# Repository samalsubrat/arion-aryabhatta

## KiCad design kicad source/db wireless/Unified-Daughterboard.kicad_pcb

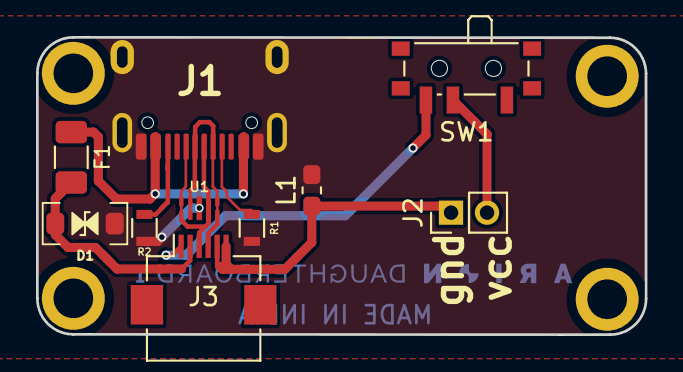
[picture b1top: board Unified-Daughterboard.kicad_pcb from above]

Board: 2 copper layers, 33.8 x 16.5 mm, 14 parts (0 on the bottom side), 10 nets.

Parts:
D1: SMF9.0CA; D_SOD-123_Bidirectional
F1: ASMD1206-150; Fuse_1206_3216Metric
J1: TYPE-C-31-M12_13; TYPE-C-31-M-12
J2: Conn_01x02_Socket; PinHeader_1x02_P2.00mm_Vertical
J3: Conn_01x06_Pin; Hirose_FH12-6S-0.5SH_1x06-1MP_P0.50mm_Horizontal
L1: 60R@100MHz; L_0603_1608Metric_Pad1.05x0.95mm_HandSolder
MH1, MH3, MH4, MH4#2: Mount-M2; Generic-Mounthole
R1, R2: 5.1k; R_0603
SW1: SW_DPDT_x2; SW_SPDT_PCM12
U1: TPD4E05U06DQAR; USON-10_2.5x1.0mm_P0.5mm

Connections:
DA+: J1.A6 (D+), J1.B6 (D+), J3.3, U1.1 (IO1), U1.4 (D2+), U1.7 (NC), U1.10 (NC)
DA-: J1.A7 (D-), J1.B7 (D-), J3.4, U1.2 (IO2), U1.5 (D2-), U1.6 (NC), U1.9 (NC)
GND: J2.1, J3.5, J3.6, L1.1
GNDPWR: D1.1 (A1), J1.A1 (GND), J1.B1 (GND), J1.S (SHIELD), L1.2, R1.2, R2.2, U1.3 (GND), U1.8 (GND)
unnamed: J1.A5 (CC1), R1.1
unnamed: J1.B5 (CC2), R2.1
VBUS: F1.1, J1.A4 (VBUS), J1.B4 (VBUS)
VCC: D1.2 (A2), F1.2, J3.2
bat in: J2.2, SW1.2 (B)
bat+: J3.1, SW1.3 (C)

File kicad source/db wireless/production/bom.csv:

+//3//f/9-Designator,Footprint,Quantity,Value,LCSC Part +ACM-
D1,D+AF8-SOD+AC0-123+AF8-Bidirectional,1,SMF9.0CA,
F1,1206,1,ASMD1206+AC0-150,
J1,TYPE+AC0-C+AC0-31+AC0-M+AC0-12,1,TYPE+AC0-C+AC0-31+AC0-M12+AF8-13,
J2,PinHeader+AF8-1x02+AF8-P2.54mm+AF8-Vertical,1,Conn+AF8-01x02+AF8-Socket,
J3,Hirose+AF8-FH12+AC0-6S+AC0-0.5SH+AF8-1x06+AC0-1MP+AF8-P0.50mm+AF8-Horizontal,1,Conn+AF8-01x06+AF8-Pin,
L1,603,1,60R+AEA-100MHz,
+ACI-MH1, MH3, MH4+AF8-2, MH4+ACI-,Generic+AC0-Mounthole,4,Mount+AC0-M2,
+ACI-R1, R2+ACI-,R+AF8-0603,2,5.1k,
SW1,SW+AF8-SPDT+AF8-PCM12,1,MSK12C02,
U1,USON+AC0-10+AF8-2.5x1.0mm+AF8-P0.5mm,1,TPD4E05U06DQAR,

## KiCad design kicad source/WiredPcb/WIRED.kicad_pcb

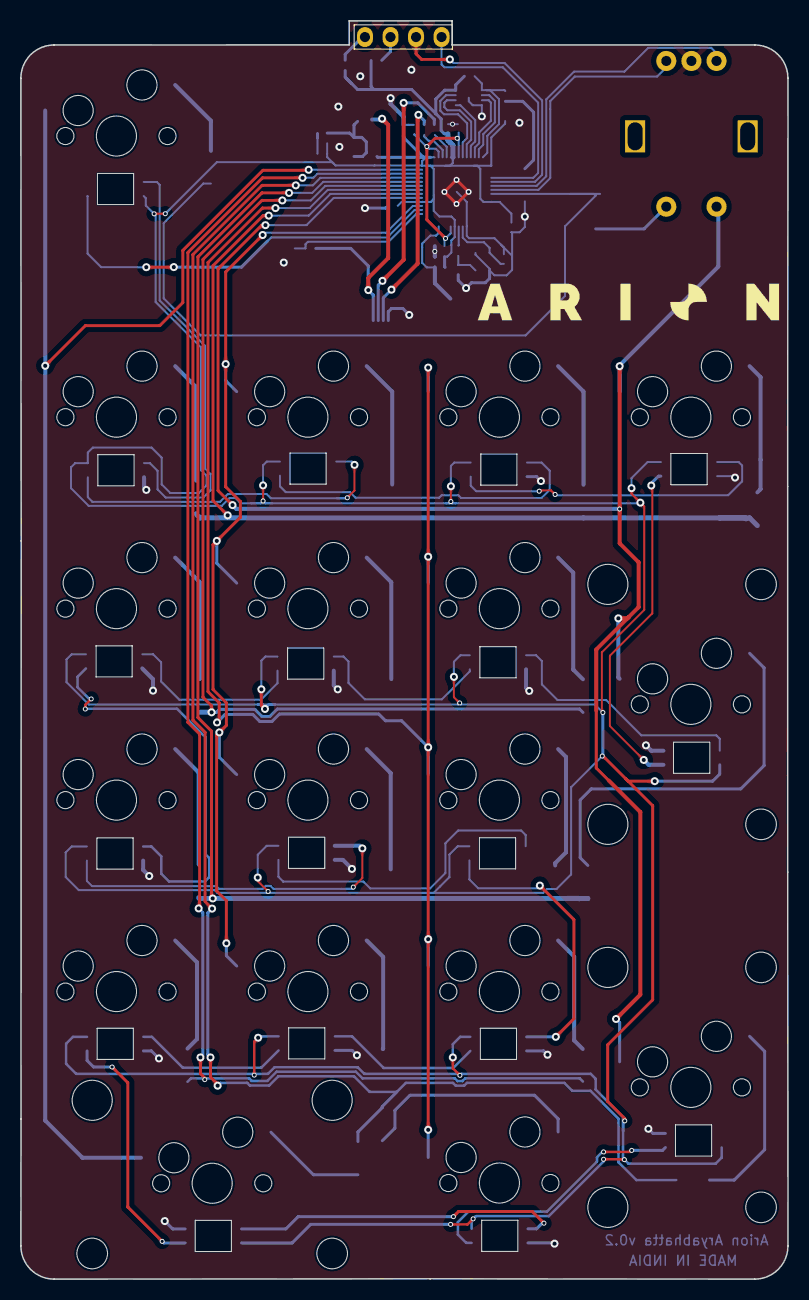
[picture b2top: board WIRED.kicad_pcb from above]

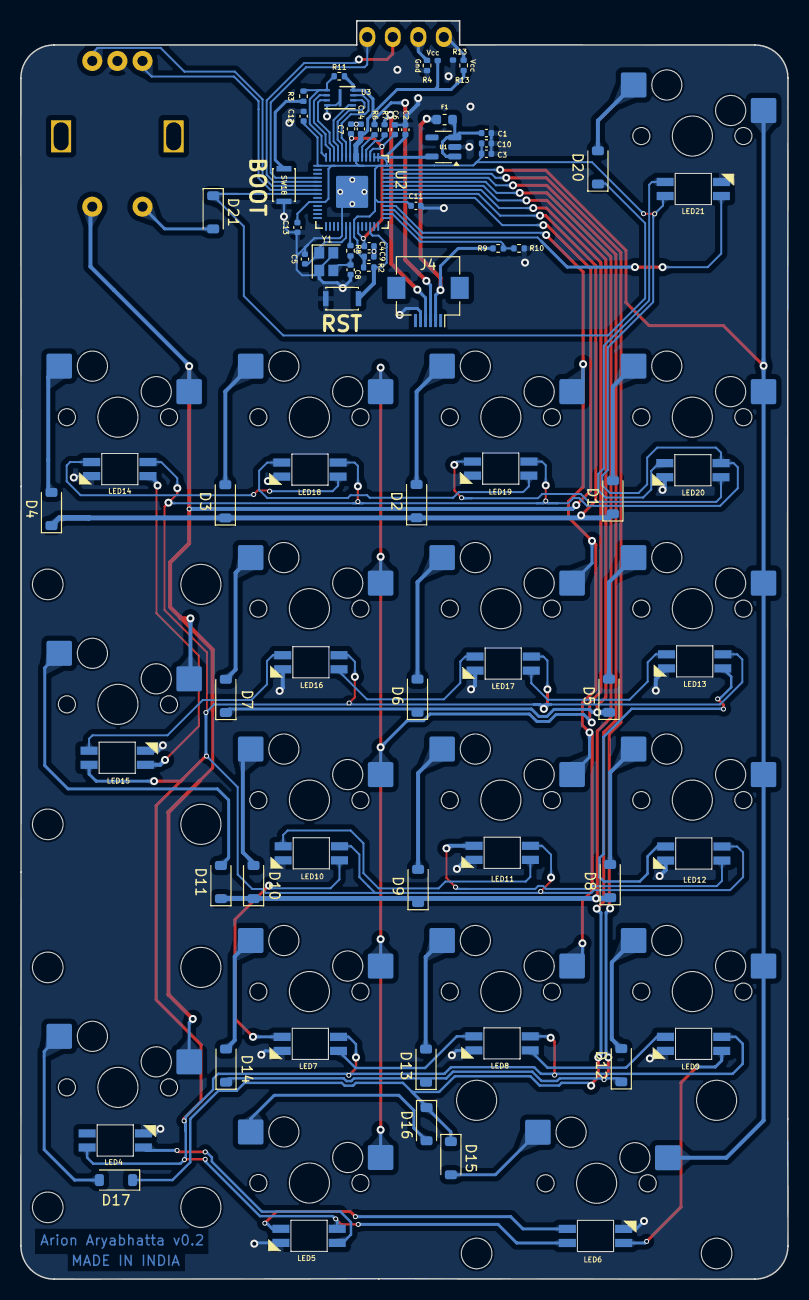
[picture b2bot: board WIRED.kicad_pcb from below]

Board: 2 copper layers, 76.3 x 125.2 mm, 91 parts (89 on the bottom side), 74 nets.

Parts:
C1, C2, C3, C4: 1µ; C_0402_1005Metric
C5, C8: 15p; C_0402_1005Metric
C6, C7, C9, C10, C11, C12, C13, C14: 100n; C_0402_1005Metric
D1, D2, D3, D4, D5, D6, D7, D8, D9, D10, D11, D12, D13, D14, D15, D16, D17, D20, D21: 1N4148W; D_SOD-123
F1: Polyfuse; Fuse_0603_1608Metric
J3: Conn_01x04_Pin; 128x64OLED
J4: Conn_01x06_Socket; Hirose_FH12-6S-0.5SH_1x06-1MP_P0.50mm_Horizontal
LED4, LED5, LED6, LED7, LED8, LED9, LED10, LED11, LED12, LED13, LED14, LED15, LED16, LED17, LED18, LED19, LED20, LED21: YS-SK6812MINI-E
R1, R4, R12, R13: 0k; R_0402_1005Metric
R2, R10, R11: 10k; R_0402_1005Metric
R3, R8: 1k; R_0402_1005Metric
R6, R7: 27; R_0402_1005Metric
R9: 5.1k; R_0402_1005Metric
SW0, SW1, SW2, SW3, SW4, SW5, SW6, SW8, SW9, SW10, SW11, SW12, SW13, SW16, SW20: KEYSW; MX-Hotswap-1U
SW7, SW14: KEYSW; MX-Hotswap-2U-Vertical-ReversedStabilizers
SW15: KEYSW; MX-Hotswap-2U-ReversedStabilizers
SW17, SW18: SW_Push; SW_SPST_CK_KXT3
SW19: Rotary_Encoder_Switch; RotaryEncoder_Alps_EC11E-Switch_Vertical_H20mm-keebio_modif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
U1: XC6210B332MR-G; SOT-23-5
U2: U2; QFN-56-1EP_7x7mm_P0.4mm_EP3.2x3.2mm
U3: U3; USON-8-1EP_3x2mm_P0.5mm_EP0.25x1.65mm
Y1: Crystal_GND24; Crystal_SMD_2520-4Pin_2.5x2.0mm

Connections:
+1V1: C4.1, C6.1, C7.1, U2.23 (DVDD), U2.45 (VREG_VOUT), U2.50 (DVDD)
+3V3: C2.1, C3.1, C9.1, C10.1, C11.1, C12.1, C13.1, C14.1, LED4.1 (VDD), LED5.1 (VDD), LED6.1 (VDD), LED7.1 (VDD), LED8.1 (VDD), LED9.1 (VDD), LED10.1 (VDD), LED11.1 (VDD), LED12.1 (VDD), LED13.1 (VDD), LED14.1 (VDD), LED15.1 (VDD), LED16.1 (VDD), LED17.1 (VDD), LED18.1 (VDD), LED19.1 (VDD), LED20.1 (VDD), LED21.1 (VDD), R1.2, R2.2, R11.2, R13.2, U1.5 (VOUT), U2.1 (IOVDD), U2.10 (IOVDD), U2.22 (IOVDD), U2.33 (IOVDD), U2.42 (IOVDD), U2.43 (ADC_AVDD), U2.44 (VREG_IN), U2.48 (USB_VDD), U2.49 (IOVDD), U3.8 (VCC)
+5V: C1.1, F1.2, U1.1 (VIN), U1.3 (EN)
/D+: J4.3, R6.1
/D-: J4.4, R7.1
/QSPI_D0: U2.53 (QSPI_SD0), U3.5 (DI(IO0))
/QSPI_D1: U2.55 (QSPI_SD1), U3.2 (DO(IO1))
/QSPI_D2: U2.54 (QSPI_SD2), U3.3 (IO2)
/QSPI_D3: U2.51 (QSPI_SD3), U3.7 (IO3)
/QSPI_SCLK: U2.52 (QSPI_SCLK), U3.6 (CLK)
/QSPI_~CS: R3.2, R11.1, U2.56 (QSPI_SS), U3.1 (~CS)
/VBUS_DET: R9.1, R10.2, U2.30 (GPIO19)
/~RESET: R2.1, SW17.2, U2.26 (RUN/~RST)
ENCA: SW19.A, U2.6 (GPIO4)
ENCB: SW19.B, U2.7 (GPIO5)
GND: C1.2, C2.2, C3.2, C4.2, C5.2, C6.2, C7.2, C8.2, C9.2, C10.2, C11.2, C12.2, C13.2, C14.2, J4.5, LED4.3 (VSS), LED5.3 (VSS), LED6.3 (VSS), LED7.3 (VSS), LED8.3 (VSS), LED9.3 (VSS), LED10.3 (VSS), LED11.3 (VSS), LED12.3 (VSS), LED13.3 (VSS), LED14.3 (VSS), LED15.3 (VSS), LED16.3 (VSS), LED17.3 (VSS), LED18.3 (VSS), LED19.3 (VSS), LED20.3 (VSS), LED21.3 (VSS), R4.1, R10.1, R12.1, SW17.1, SW18.1, SW19.C, U1.2 (GND), U2.19 (TESTEN), U2.57 (GND), U3.4 (GND), U3.9 (EP), Y1.2, Y1.4
LEDIN: LED21.4 (DIN), U2.31 (GPIO20)
unnamed: C8.1, R8.1, Y1.3
unnamed: D1.2 (A), SW0.2
unnamed: D2.2 (A), SW1.2
unnamed: D3.2 (A), SW2.2
unnamed: D4.2 (A), SW3.2
unnamed: D5.2 (A), SW4.2
unnamed: D6.2 (A), SW5.2
unnamed: D7.2 (A), SW6.2
unnamed: D8.2 (A), SW8.2
unnamed: D9.2 (A), SW9.2
unnamed: D10.2 (A), SW10.2
unnamed: D11.2 (A), SW7.2
unnamed: D12.2 (A), SW11.2
unnamed: D13.2 (A), SW12.2
unnamed: D14.2 (A), SW13.2
unnamed: D15.2 (A), SW15.2
unnamed: D16.2 (A), SW16.2
unnamed: D17.2 (A), SW14.2
unnamed: D20.2 (A), SW20.2
unnamed: D21.2 (A), SW19.S1
unnamed: J3.1, R13.1
unnamed: J3.2, R4.2
unnamed: LED4.4 (DIN), LED5.2 (DOUT)
unnamed: LED5.4 (DIN), LED6.2 (DOUT)
unnamed: LED6.4 (DIN), LED9.2 (DOUT)
unnamed: LED7.2 (DOUT), LED8.4 (DIN)
unnamed: LED8.2 (DOUT), LED9.4 (DIN)
unnamed: LED10.4 (DIN), LED11.2 (DOUT)
unnamed: LED7.4 (DIN), LED10.2 (DOUT)
unnamed: LED11.4 (DIN), LED12.2 (DOUT)
unnamed: LED12.4 (DIN), LED13.2 (DOUT)
unnamed: LED13.4 (DIN), LED17.2 (DOUT)
unnamed: LED14.4 (DIN), LED18.2 (DOUT)
unnamed: LED14.2 (DOUT), LED15.4 (DIN)
unnamed: LED15.2 (DOUT), LED16.4 (DIN)
unnamed: LED16.2 (DOUT), LED17.4 (DIN)
unnamed: LED18.4 (DIN), LED19.2 (DOUT)
unnamed: LED19.4 (DIN), LED20.2 (DOUT)
unnamed: LED20.4 (DIN), LED21.2 (DOUT)
unnamed: R3.1, SW18.2
unnamed: R7.2, U2.46 (USB_DM)
unnamed: R6.2, U2.47 (USB_DP)
unnamed: C5.1, U2.20 (XIN), Y1.1
unnamed: R8.2, U2.21 (XOUT)
VBUS: F1.1, J4.2, R9.2
col0: SW0.1, SW4.1, SW8.1, SW11.1, SW15.1, SW20.1, U2.41 (GPIO29_ADC3)
col1: SW1.1, SW5.1, SW9.1, SW12.1, U2.32 (GPIO21)
col2: SW2.1, SW6.1, SW10.1, SW13.1, SW16.1, U2.36 (GPIO24)
col3: SW3.1, SW7.1, SW14.1, SW19.S2, U2.34 (GPIO22)
row0: D1.1 (K), D2.1 (K), D3.1 (K), D4.1 (K), U2.35 (GPIO23)
row1: D5.1 (K), D6.1 (K), D7.1 (K), U2.37 (GPIO25)
row2: D8.1 (K), D9.1 (K), D10.1 (K), D11.1 (K), U2.38 (GPIO26_ADC0)
row3: D12.1 (K), D13.1 (K), D14.1 (K), U2.40 (GPIO28_ADC2)
row4: D15.1 (K), D16.1 (K), D17.1 (K), U2.39 (GPIO27_ADC1)
row5: D20.1 (K), D21.1 (K), U2.8 (GPIO6)
sda: J3.4, U2.4 (GPIO2)
sdl: J3.3, U2.5 (GPIO3)

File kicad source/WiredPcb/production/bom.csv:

+//3//f/9-Designator,Footprint,Quantity,Value,LCSC Part +ACM-
+ACI-C1, C2+ACI-,402,2,1U,C19666
+ACI-C10, C11, C12, C13, C14, C6, C7, C9+ACI-,402,8,100n,C1525
+ACI-C3, C4+ACI-,402,2,1U,C52923
+ACI-C5, C8+ACI-,402,2,15p,C1548
+ACI-D1, D10, D11, D12, D13, D14, D15, D16, D17, D2, D20, D21, D3, D4, D5, D6, D7, D8, D9+ACI-,D+AF8-SOD+AC0-123,19,1N4148W,
F1,603,1,Polyfuse,C69679
,,,,
J4,Hirose+AF8-FH12+AC0-6S+AC0-0.5SH+AF8-1x06+AC0-1MP+AF8-P0.50mm+AF8-Horizontal,1,Conn+AF8-01x06+AF8-Socket,
+ACI-LED10, LED11, LED12, LED13, LED14, LED15, LED16, LED17, LED18, LED19, LED20, LED21, LED4, LED5, LED6, LED7, LED8, LED9+ACI-,YS+AC0-SK6812MINI+AC0-E,18,SK6812MINI+AC0-E,
,,,,
+ACI-R10, R11, R2+ACI-,402,3,10k,C25744
+ACI-R3, R8+ACI-,402,2,1k,C11702
+ACI-R6, R7+ACI-,402,2,27,C25100
R9,402,1,5.1k,C25905
+ACI-SW0, SW1, SW10, SW11, SW12, SW13, SW16, SW2, SW20, SW3, SW4, SW5, SW6, SW8, SW9+ACI-,MXOnly+AC0-1U+AC0-Hotswap+AC0-Antishear,15,KEYSW,
+ACI-SW14, SW15, SW7+ACI-,MXOnly+AC0-2U+AC0-Hotswap,3,KEYSW,
+ACI-SW17, SW18+ACI-,SW+AF8-SPST+AF8-CK+AF8-KXT3,2,SW+AF8-Push,C319433
SW19,RotaryEncoder+AF8-Alps+AF8-EC11E+AC0-Switch+AF8-Vertical+AF8-H20mm+AC0-keebio+AF8-modified,1,Rotary+AF8-Encoder+AF8-Switch,
U1,SOT+AC0-23+AC0-5,1,XC6210B332MR+AC0-G,C82942
U2,QFN+AC0-56+AC0-1EP+AF8-7x7mm+AF8-P0.4mm+AF8-EP3.2x3.2mm,1,RP2040,C2040
U3,USON+AC0-8+AC0-1EP+AF8-3x2mm+AF8-P0.5mm+AF8-EP0.25x1.65mm,1,W25Q16JVUXIQ,C2843335
Y1,Crystal+AF8-SMD+AF8-2520+AC0-4Pin+AF8-2.5x2.0mm,1,Crystal+AF8-GND24,C2149204

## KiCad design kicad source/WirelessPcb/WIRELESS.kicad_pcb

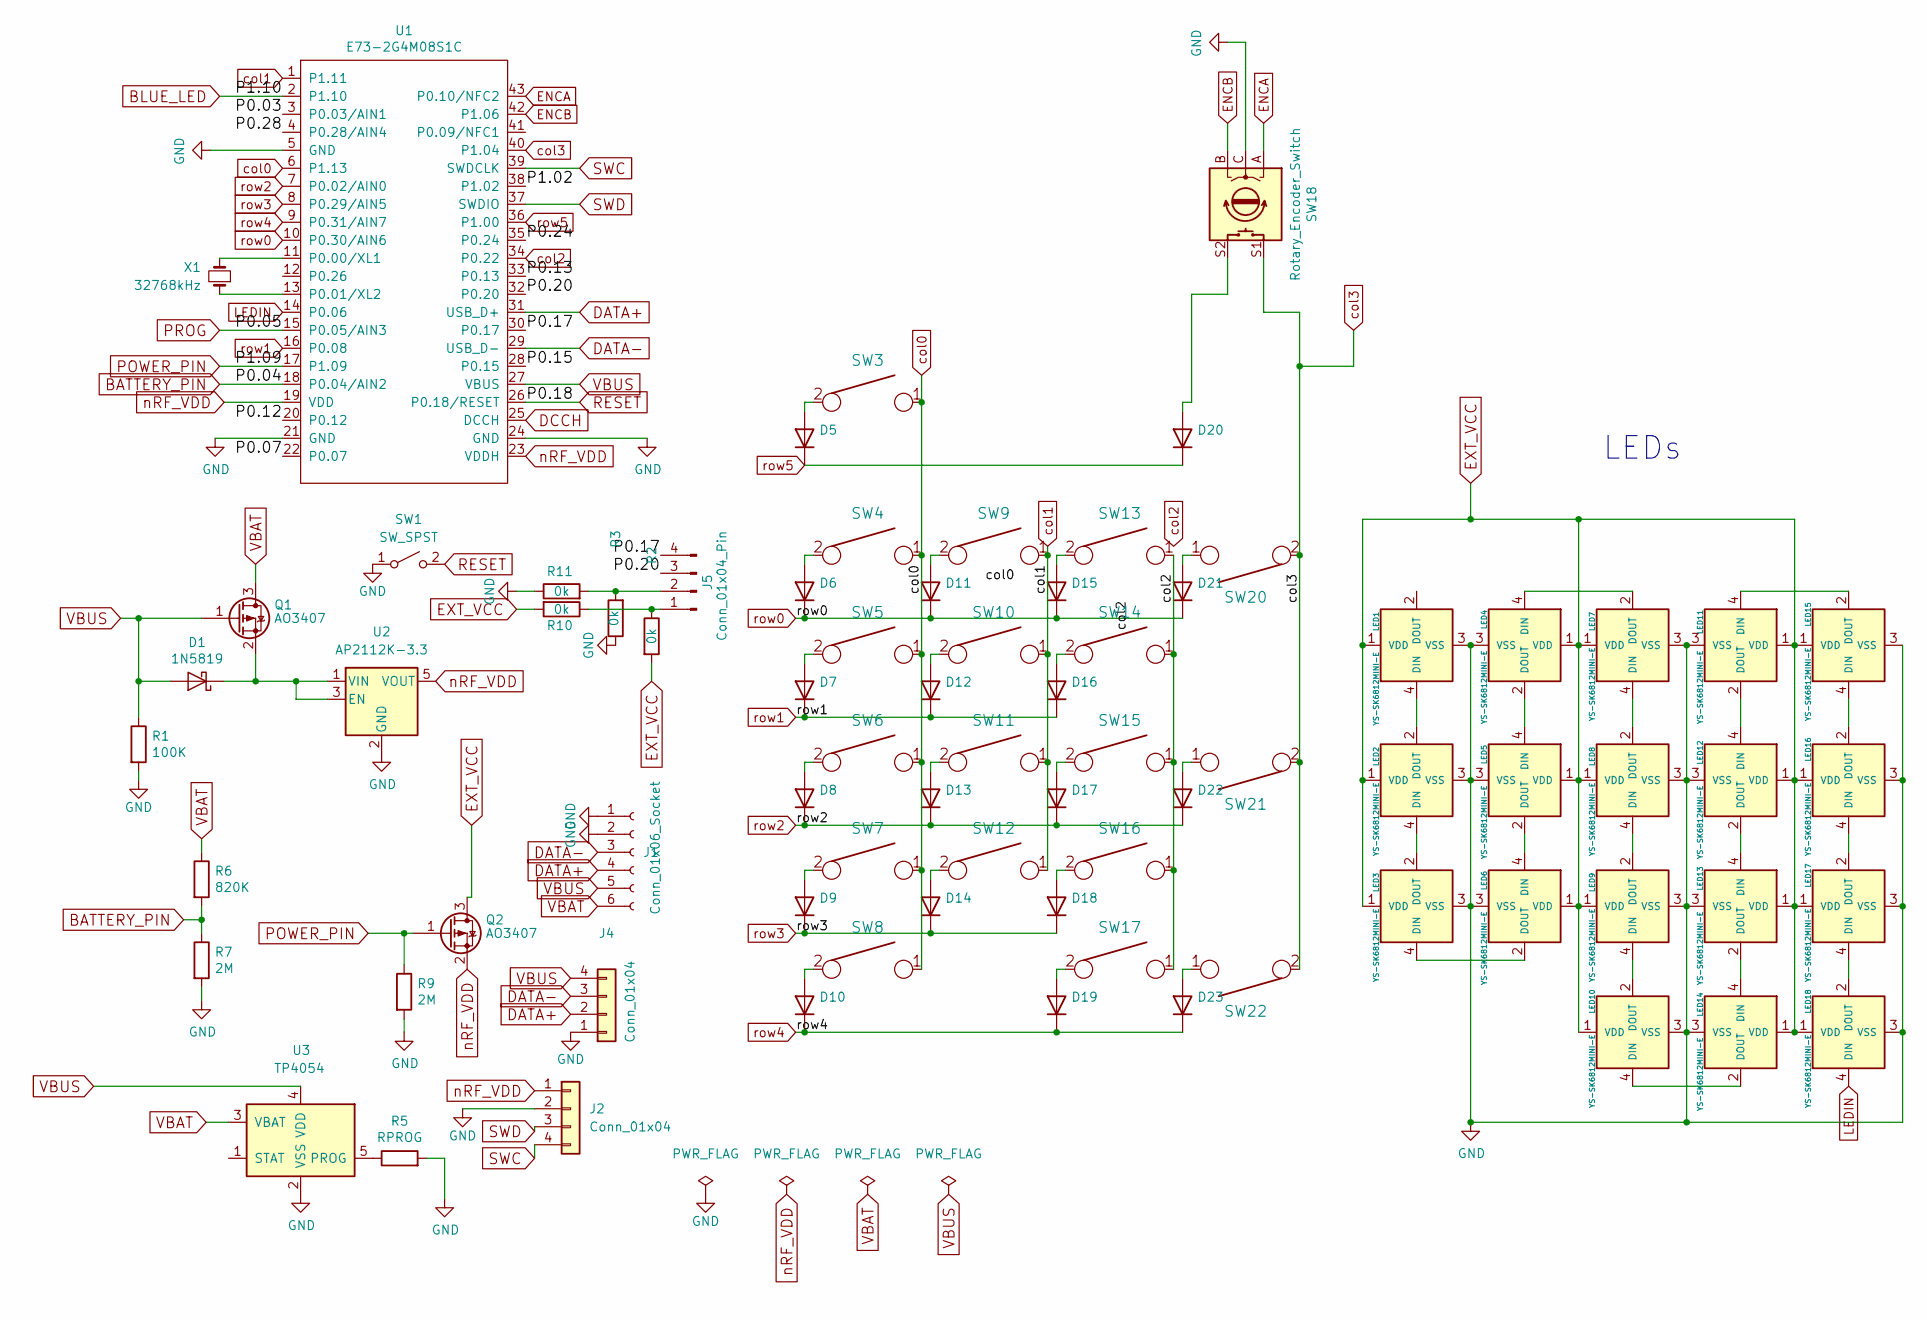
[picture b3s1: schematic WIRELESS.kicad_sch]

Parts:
D1: 1N5819; D_SOD-323F
D5, D6, D7, D8, D9, D10, D11, D12, D13, D14, D15, D16, D17, D18, D19, D20, D21, D22, D23: D_SOD-123
J1: Conn_01x06_Socket; Hirose_FH12-6S-0.5SH_1x06-1MP_P0.50mm_Horizontal
J2, J4: Conn_01x04; PinHeader_1x04_P2.54mm_Vertical
J5: Conn_01x04_Pin; PinHeader_1x04_P2.54mm_Vertical
LED1, LED2, LED3, LED4, LED5, LED6, LED7, LED8, LED9, LED10, LED11, LED12, LED13, LED14, LED15, LED16, LED17, LED18: YS-SK6812MINI-E
Q1, Q2: AO3407; SOT-23
R1: 100K; R_0603_1608Metric
R2, R3, R10, R11: 0k; R_0402_1005Metric; LCSC C25744
R5: RPROG; R_0603_1608Metric
R6: 820K; R_0603_1608Metric
R7, R9: 2M; R_0603_1608Metric
SW1: SW_SPST; SW_SPST_CK_KXT3
SW3, SW4, SW5, SW6, SW7, SW9, SW10, SW11, SW12, SW13, SW14, SW15, SW16, SW17, SW20: KEYSW; MX-Hotswap-1U
SW8: KEYSW; MX-Hotswap-2U-ReversedStabilizers
SW18: Rotary_Encoder_Switch; RotaryEncoder_Alps_EC11E-Switch_Vertical_H20mm-keebio_modif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
SW21, SW22: KEYSW; MX-Hotswap-2U-Vertical-ReversedStabilizers
U1: E73-2G4M08S1C; E73-2G4M08S1C-52840
U2: AP2112K-3.3; SOT-23-5
U3: TP4054; SOT-23-5
X1: 32768kHz

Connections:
/P0.03: U1.3 (P0.03/AIN1)
/P0.07: U1.22 (P0.07)
/P0.12: U1.20 (P0.12)
/P0.13: U1.33 (P0.13)
/P0.15: U1.28 (P0.15)
/P0.17: J5.4, U1.30 (P0.17)
/P0.20: J5.3, U1.32 (P0.20)
/P0.24: U1.35 (P0.24)
/P0.28: U1.4 (P0.28/AIN4)
/P1.02: U1.38 (P1.02)
BATTERY_PIN: R6.2, R7.1, U1.18 (P0.04/AIN2)
BLUE_LED: U1.2 (P1.10)
DATA+: J1.4, J4.2, U1.31 (USB_D+)
DATA-: J1.3, J4.3, U1.29 (USB_D-)
DCCH: U1.25 (DCCH)
ENCA: SW18.A, U1.43 (P0.10/NFC2)
ENCB: SW18.B, U1.42 (P1.06)
EXT_VCC: LED1.1 (VDD), LED2.1 (VDD), LED3.1 (VDD), LED4.1 (VDD), LED5.1 (VDD), LED6.1 (VDD), LED7.1 (VDD), LED8.1 (VDD), LED9.1 (VDD), LED10.1 (VDD), LED11.1 (VDD), LED12.1 (VDD), LED13.1 (VDD), LED14.1 (VDD), LED15.1 (VDD), LED16.1 (VDD), LED17.1 (VDD), LED18.1 (VDD), Q2.3 (D), R2.2, R10.2
GND: J1.1, J1.2, J2.2, J4.1, LED1.3 (VSS), LED2.3 (VSS), LED3.3 (VSS), LED4.3 (VSS), LED5.3 (VSS), LED6.3 (VSS), LED7.3 (VSS), LED8.3 (VSS), LED9.3 (VSS), LED10.3 (VSS), LED11.3 (VSS), LED12.3 (VSS), LED13.3 (VSS), LED14.3 (VSS), LED15.3 (VSS), LED16.3 (VSS), LED17.3 (VSS), LED18.3 (VSS), R1.2, R3.1, R5.2, R7.2, R9.2, R11.1, SW1.1 (A), SW18.C, U1.5 (GND), U1.21 (GND), U1.24 (GND), U2.2 (GND), U3.2 (VSS); also elsewhere on the board
LEDIN: LED18.4 (DIN), U1.14 (P0.06)
unnamed: D1.1 (K), Q1.2 (S), U2.1 (VIN), U2.3 (EN)
unnamed: D5.2 (A), SW3.2
unnamed: D6.2 (A), SW4.2
unnamed: D7.2 (A), SW5.2
unnamed: D8.2 (A), SW6.2
unnamed: D9.2 (A), SW7.2
unnamed: D10.2 (A), SW8.2
unnamed: D11.2 (A), SW9.2
unnamed: D12.2 (A), SW10.2
unnamed: D13.2 (A), SW11.2
unnamed: D14.2 (A), SW12.2
unnamed: D15.2 (A), SW13.2
unnamed: D16.2 (A), SW14.2
unnamed: D17.2 (A), SW15.2
unnamed: D18.2 (A), SW16.2
unnamed: D19.2 (A), SW17.2
unnamed: D20.2 (A), SW18.S2
unnamed: D21.2 (A), SW20.1
unnamed: D22.2 (A), SW21.1
unnamed: D23.2 (A), SW22.1
unnamed: J5.1, R2.1, R10.1
unnamed: J5.2, R3.2, R11.2
unnamed: LED1.4 (DIN), LED2.2 (DOUT)
unnamed: LED2.4 (DIN), LED3.2 (DOUT)
unnamed: LED3.4 (DIN), LED6.2 (DOUT)
unnamed: LED4.4 (DIN), LED7.2 (DOUT)
unnamed: LED4.2 (DOUT), LED5.4 (DIN)
unnamed: LED5.2 (DOUT), LED6.4 (DIN)
unnamed: LED7.4 (DIN), LED8.2 (DOUT)
unnamed: LED8.4 (DIN), LED9.2 (DOUT)
unnamed: LED10.4 (DIN), LED14.2 (DOUT)
unnamed: LED9.4 (DIN), LED10.2 (DOUT)
unnamed: LED11.4 (DIN), LED15.2 (DOUT)
unnamed: LED11.2 (DOUT), LED12.4 (DIN)
unnamed: LED12.2 (DOUT), LED13.4 (DIN)
unnamed: LED13.2 (DOUT), LED14.4 (DIN)
unnamed: LED15.4 (DIN), LED16.2 (DOUT)
unnamed: LED16.4 (DIN), LED17.2 (DOUT)
unnamed: LED17.4 (DIN), LED18.2 (DOUT)
unnamed: U1.11 (P0.00/XL1), X1.2
unnamed: U1.13 (P0.01/XL2), X1.1
unnamed: R5.1, U3.5 (PROG)
POWER_PIN: Q2.1 (G), R9.1, U1.17 (P1.09)
PROG: U1.15 (P0.05/AIN3)
RESET: SW1.2 (B), U1.26 (P0.18/RESET); also elsewhere on the board
SWC: J2.4, U1.39 (SWDCLK)
SWD: J2.3, U1.37 (SWDIO)
VBAT: J1.6, Q1.3 (D), R6.1, U3.3 (VBAT)
VBUS: D1.2 (A), J1.5, J4.4, Q1.1 (G), R1.1, U1.27 (VBUS), U3.4 (VDD)
col0: SW3.1, SW4.1, SW5.1, SW6.1, SW7.1, SW8.1, U1.6 (P1.13)
col1: SW9.1, SW10.1, SW11.1, SW12.1, U1.1 (P1.11)
col2: SW13.1, SW14.1, SW15.1, SW16.1, SW17.1, U1.34 (P0.22)
col3: SW18.S1, SW20.2, SW21.2, SW22.2, U1.40 (P1.04)
nRF_VDD: J2.1, Q2.2 (S), U1.19 (VDD), U1.23 (VDDH), U2.5 (VOUT)
row0: D6.1 (K), D11.1 (K), D15.1 (K), D21.1 (K), U1.10 (P0.30/AIN6)
row1: D7.1 (K), D12.1 (K), D16.1 (K), U1.16 (P0.08)
row2: D8.1 (K), D13.1 (K), D17.1 (K), D22.1 (K), U1.7 (P0.02/AIN0)
row3: D9.1 (K), D14.1 (K), D18.1 (K), U1.8 (P0.29/AIN5)
row4: D10.1 (K), D19.1 (K), D23.1 (K), U1.9 (P0.31/AIN7)
row5: D5.1 (K), D20.1 (K), U1.36 (P1.00)

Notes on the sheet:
LEDs

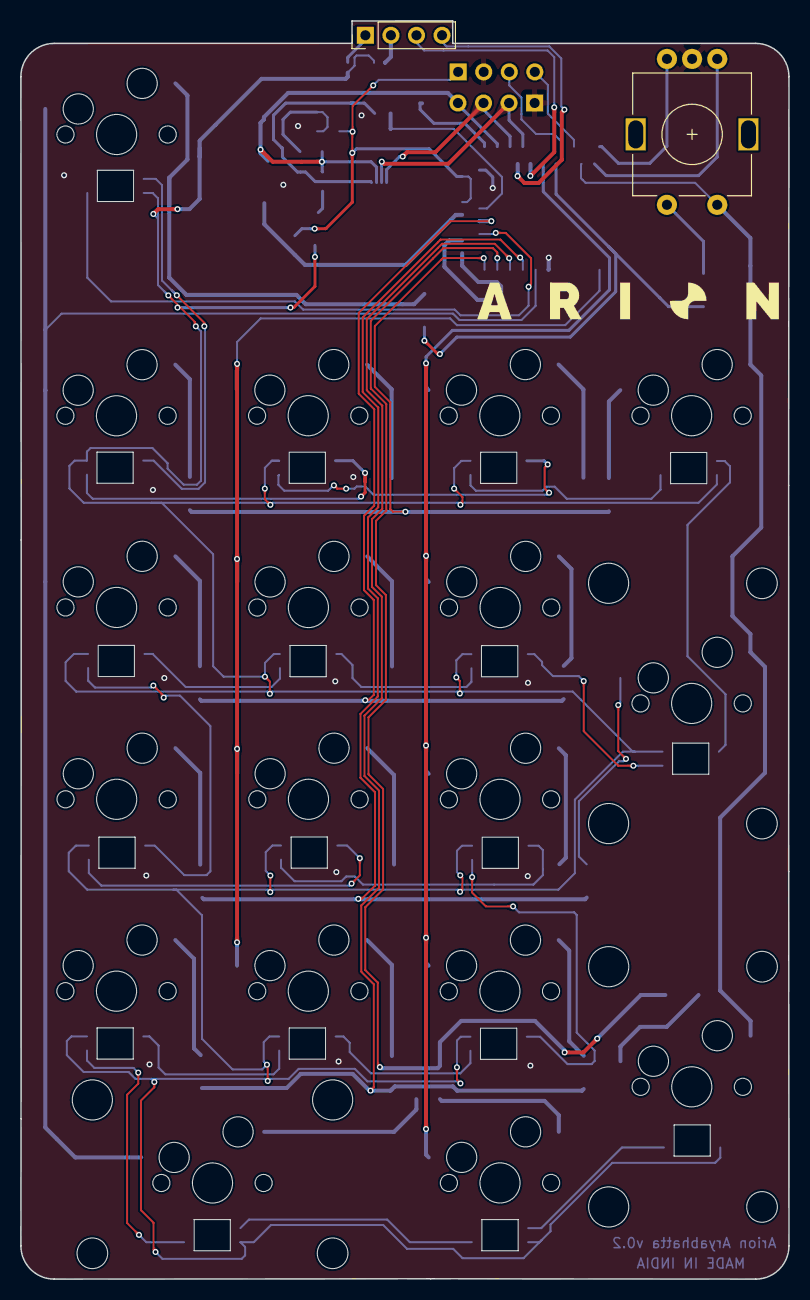
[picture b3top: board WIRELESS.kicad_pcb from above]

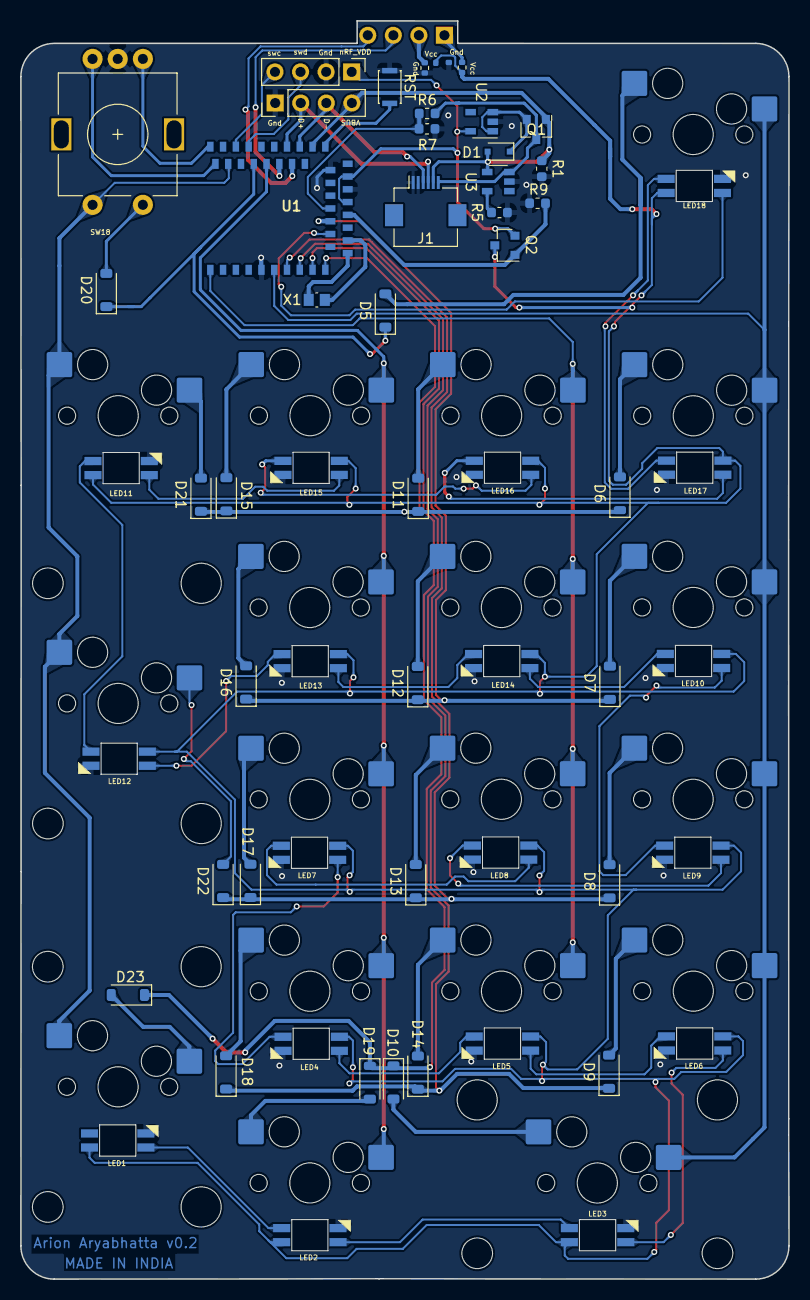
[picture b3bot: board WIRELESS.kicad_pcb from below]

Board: 2 copper layers, 76.3 x 125.0 mm, 77 parts (76 on the bottom side), 69 nets.

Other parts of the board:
RST: TS2306A; SW_SPST_CK_KXT3

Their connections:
GND: RST.1 (A); also elsewhere on the board
RESET: RST.2 (B); also elsewhere on the board

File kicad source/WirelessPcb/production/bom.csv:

Designator,Footprint,Quantity,Value,LCSC Part #
D1,D_SOD-323F,1,1N5819,
"D10, D11, D12, D13, D14, D15, D16, D17, D18, D19, D20, D21, D22, D23, D5, D6, D7, D8, D9",D_SOD-123,19,1N4148W,
J1,Hirose_FH12-6S-0.5SH_1x06-1MP_P0.50mm_Horizontal,1,Conn_01x06_Socket,C49232433
"J2, J4",PinHeader_1x04_P2.54mm_Vertical,2,Conn_01x04,
J5,PinHeader_1x04_P2.54mm_Vertical,1,Conn_01x04_Pin,
"LED1, LED10, LED11, LED12, LED13, LED14, LED15, LED16, LED17, LED18, LED2, LED3, LED4, LED5, LED6, LED7, LED8, LED9",YS-SK6812MINI-E,18,YS-SK6812MINI-E,
"Q1, Q2",SOT-23,2,AO3407,
R1,0603,1,100K,
"R10, R11, R2, R3",0402,4,0k,C25744
R5,0603,1,10k,
R6,0603,1,820K,
"R7, R9",0603,2,2M,
RST,SW_SPST_CK_KXT3,1,TS2306A ,
"SW10, SW11, SW12, SW13, SW14, SW15, SW16, SW17, SW20, SW3, SW4, SW5, SW6, SW7, SW9",MX-Hotswap-1U,15,KEYSW,
SW18,RotaryEncoder_Alps_EC11E-Switch_Vertical_H20mm-keebio_modified,1,Rotary_Encoder_Switch,C319433
"SW21, SW22",MX-Hotswap-2U-Vertical-ReversedStabilizers,2,KEYSW,
SW8,MX-Hotswap-2U-ReversedStabilizers,1,KEYSW,
U1,E73-2G4M08S1C-52840,1,E73-2G4M08S1C,C356849
U2,SOT-23-5,1,AP2112K-3.3,
U3,SOT-23-5,1,TP4054,
X1,Crystal_SMD_MicroCrystal_CM9V-T1A-2Pin_1.6x1.0mm,1,32768kHz,C5136974
